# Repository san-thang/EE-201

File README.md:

##### Sanda Thang
##### EE 201 
#### January 13, 2023

## Intro
Hey! :smile: <br>
I'm Sanda. I'm in my 3rd year

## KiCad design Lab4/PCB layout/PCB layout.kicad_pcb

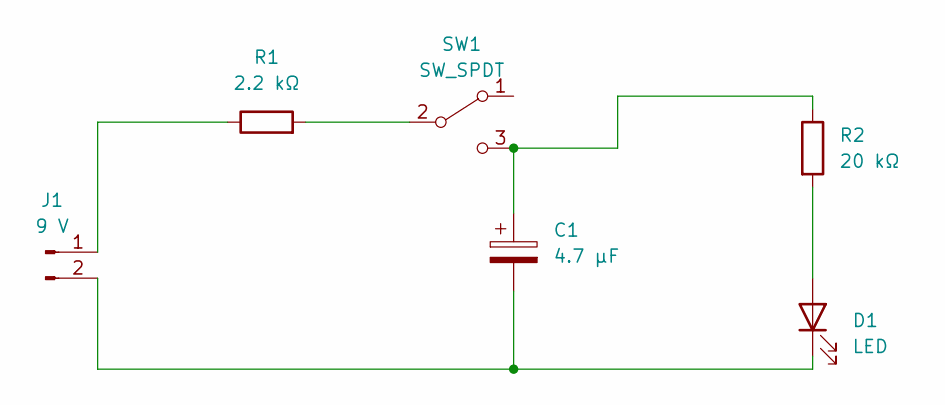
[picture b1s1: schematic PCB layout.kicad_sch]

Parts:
C1: 4.7 µF; C_Radial_D5.0mm_H5.0mm_P2.00mm
D1: LED; LED_D5.0mm
J1: 9 V; JST_PH_B2B-PH-K_1x02_P2.00mm_Vertical
R1: 2.2 kΩ; R_Axial_DIN0516_L15.5mm_D5.0mm_P20.32mm_Horizontal
R2: 20 kΩ; R_Axial_DIN0516_L15.5mm_D5.0mm_P20.32mm_Horizontal
SW1: SW_SPDT; SW_E-Switch_EG1224_SPDT_Angled

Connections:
unnamed: C1.1, R2.1, SW1.3 (C)
unnamed: C1.2, D1.1 (K), J1.2
unnamed: D1.2 (A), R2.2
unnamed: J1.1, R1.1
unnamed: R1.2, SW1.2 (B)

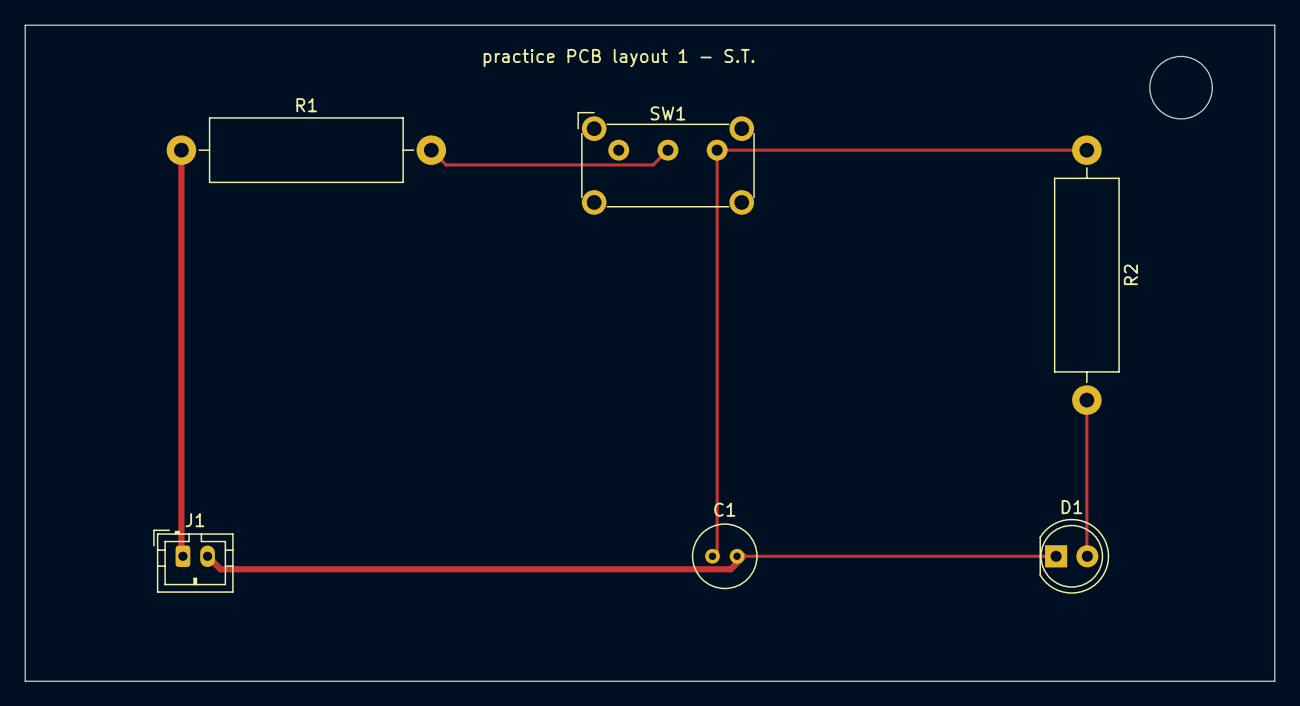
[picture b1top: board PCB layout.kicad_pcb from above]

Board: 2 copper layers, 101.6 x 53.3 mm, 6 parts (0 on the bottom side), 5 nets.

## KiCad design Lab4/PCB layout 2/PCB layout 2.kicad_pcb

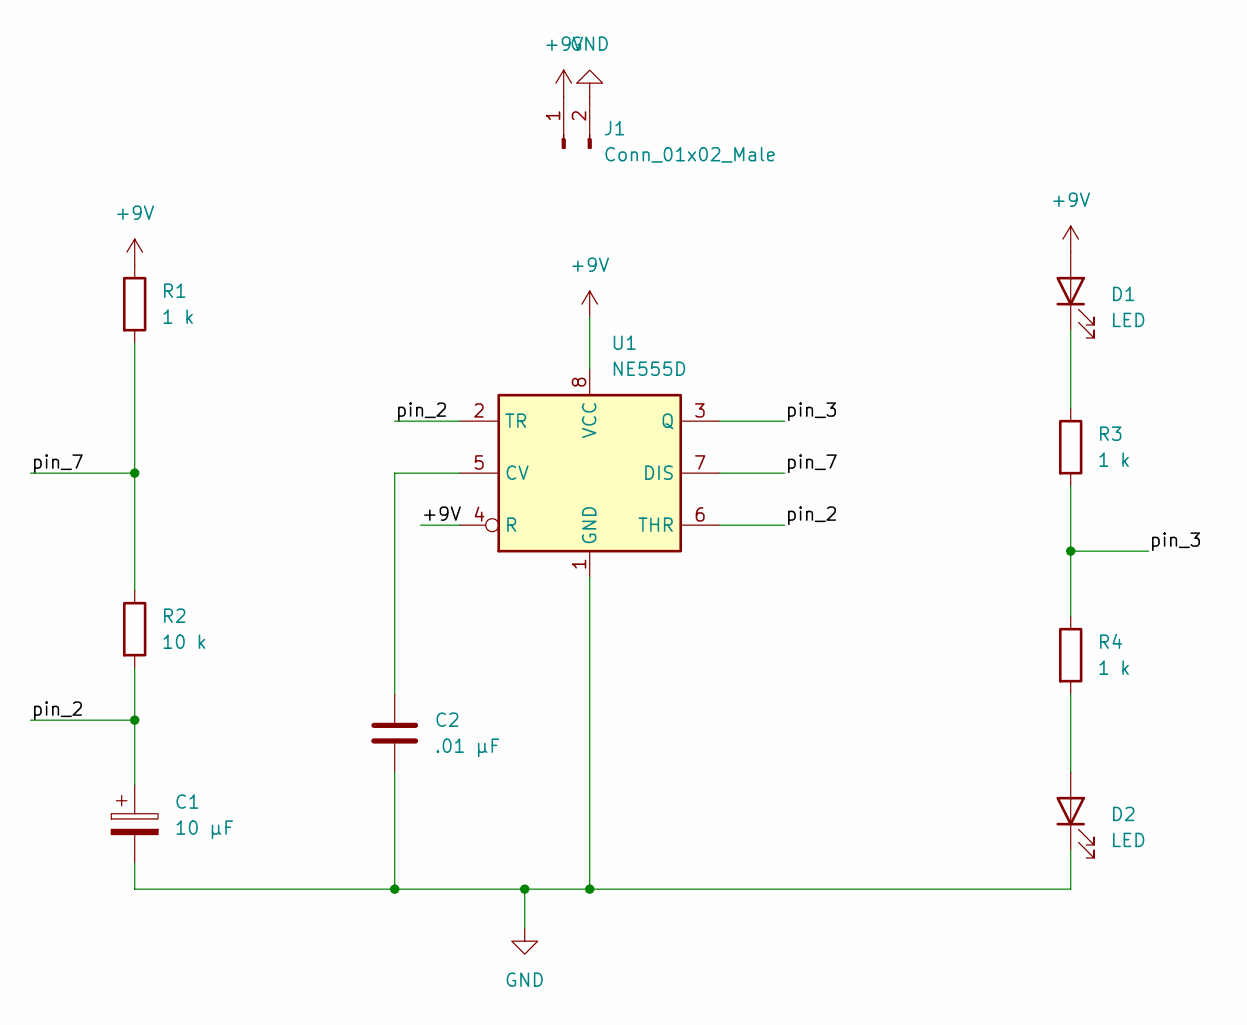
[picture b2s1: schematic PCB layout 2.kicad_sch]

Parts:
C1: 10 µF; CP_EIA-3216-18_Kemet-A_Pad1.58x1.35mm_HandSolder
C2: .01 µF; C_0805_2012Metric_Pad1.18x1.45mm_HandSolder
D1, D2: LED; LED_1206_3216Metric_Pad1.42x1.75mm_HandSolder
J1: Conn_01x02_Male; TerminalBlock_bornier-2_P5.08mm
R1, R3, R4: 1 k; R_0805_2012Metric_Pad1.20x1.40mm_HandSolder
R2: 10 k; R_0805_2012Metric_Pad1.20x1.40mm_HandSolder
U1: NE555D; SOIC-8-1EP_3.9x4.9mm_P1.27mm_EP2.29x3mm

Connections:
+9V: D1.2 (A), J1.1, R1.1, U1.4 (R), U1.8 (VCC)
/pin_2: C1.1, R2.2, U1.2 (TR), U1.6 (THR)
/pin_3: R3.2, R4.1, U1.3 (Q)
/pin_7: R1.2, R2.1, U1.7 (DIS)
GND: C1.2, C2.2, D2.1 (K), J1.2, U1.1 (GND)
unnamed: C2.1, U1.5 (CV)
unnamed: D1.1 (K), R3.1
unnamed: D2.2 (A), R4.2

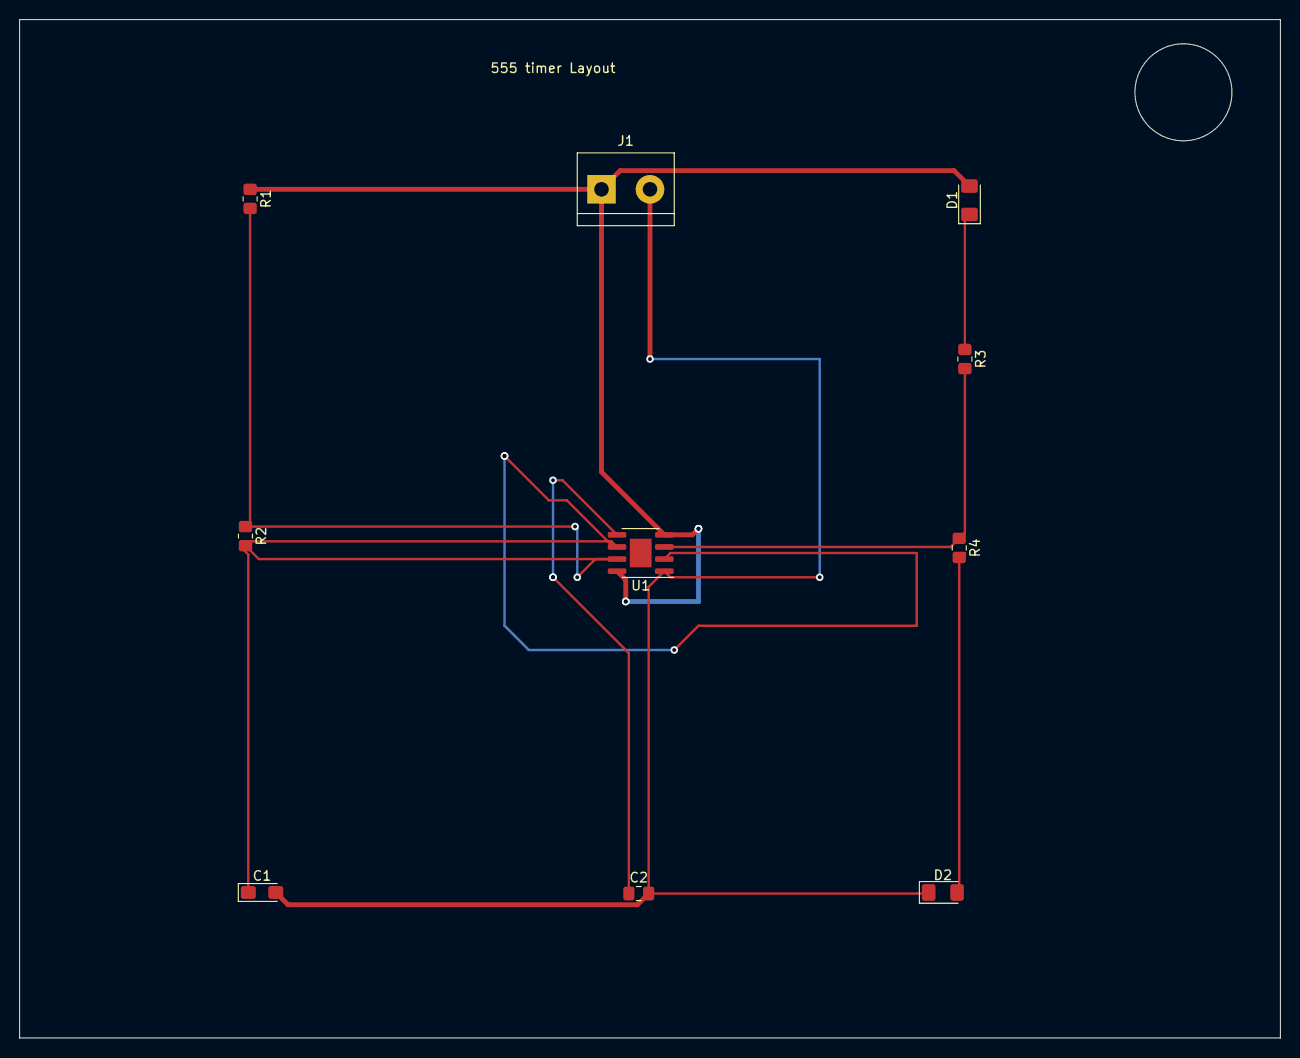
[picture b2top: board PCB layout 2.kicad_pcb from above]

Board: 2 copper layers, 132.1 x 106.7 mm, 10 parts (0 on the bottom side), 8 nets.

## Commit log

2023-01-14 added README
2023-01-14 added breakline
2023-01-14 added aboutMe directory
2023-01-14 save a breakpoint
2023-01-14 finished second paragraph
2023-01-14 adding a missing word
2023-01-14 ending
2023-01-14 added a missing letter
2023-01-20 Arduino Lab
2023-01-27 adding design 1
2023-01-27 save changes and update the designs
2023-02-03 save image
2023-02-03 save the second image
2023-02-17 save both pcb layout
2023-02-17 commit files
